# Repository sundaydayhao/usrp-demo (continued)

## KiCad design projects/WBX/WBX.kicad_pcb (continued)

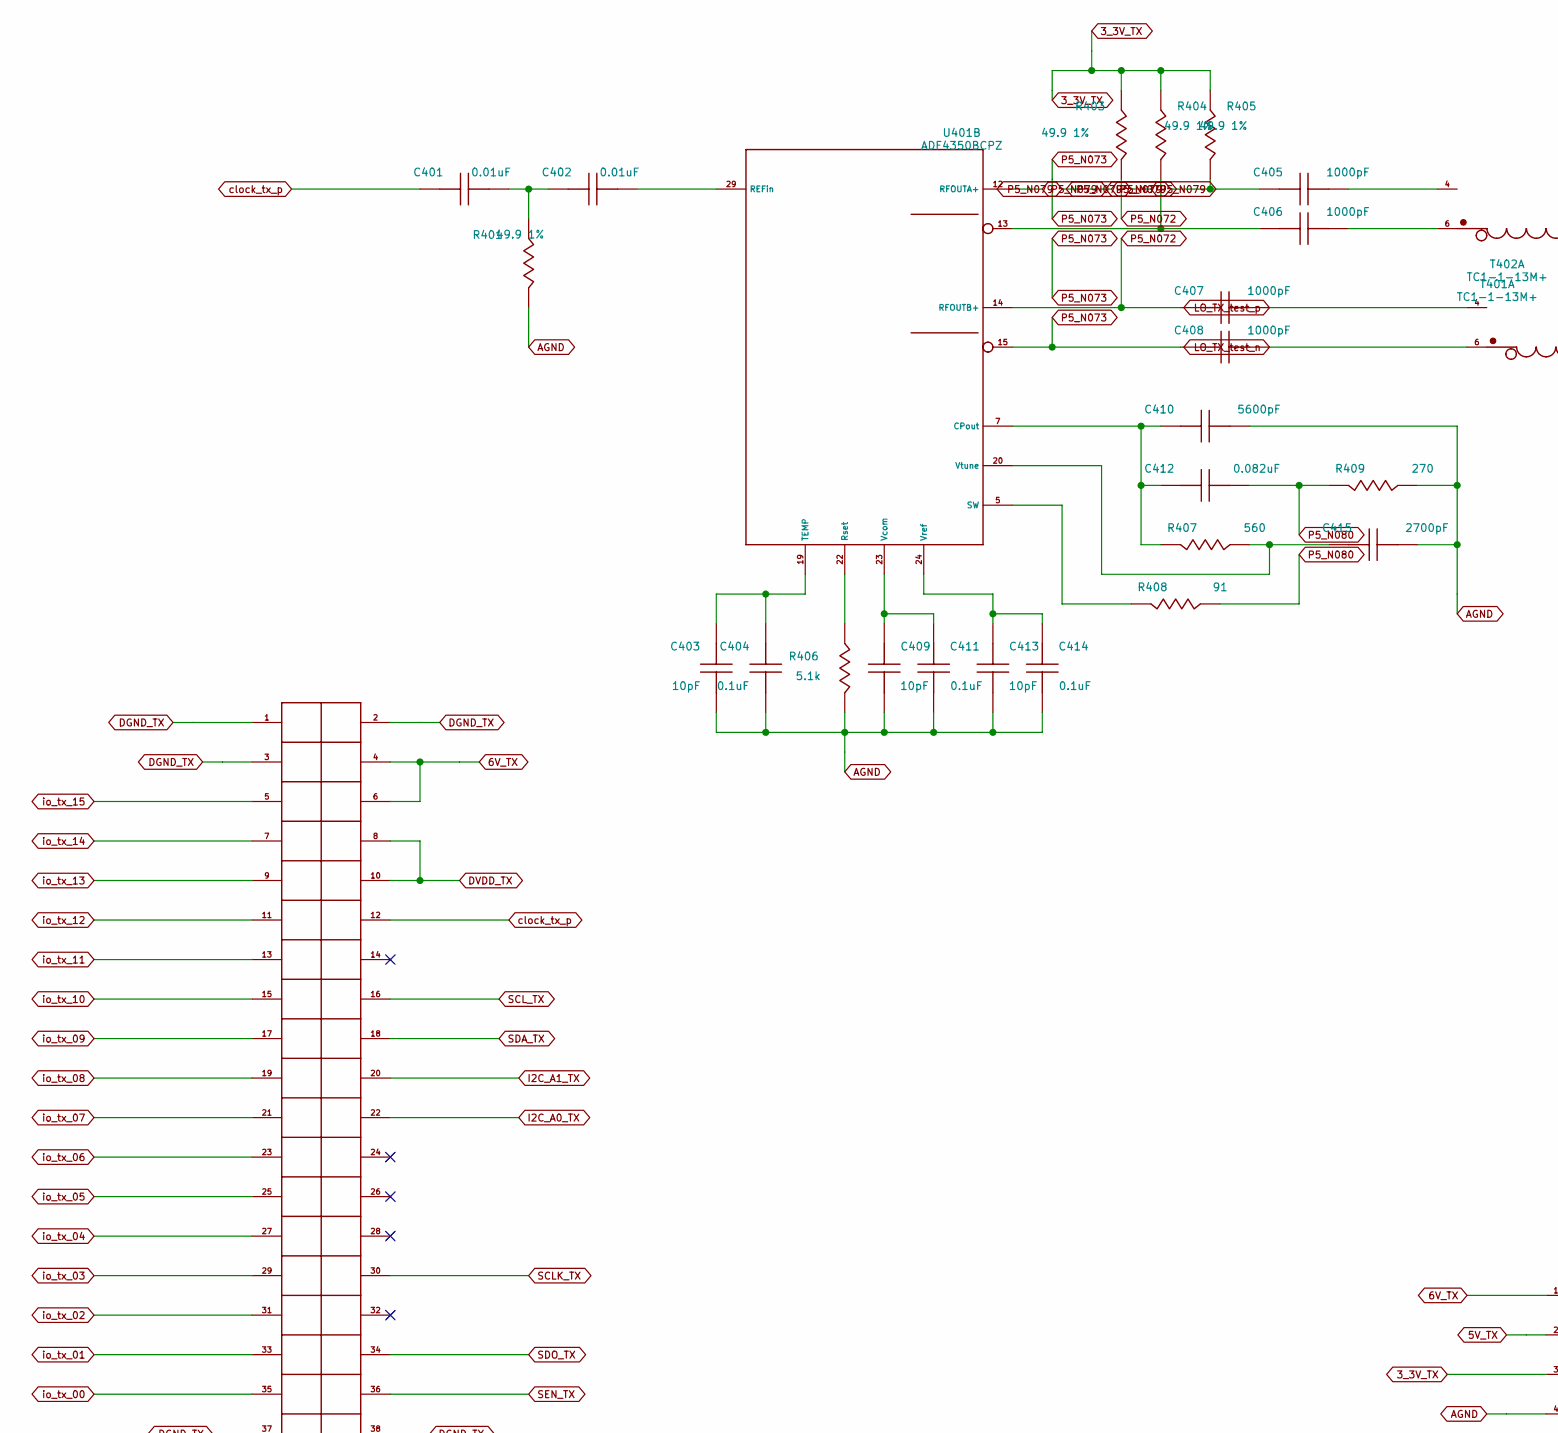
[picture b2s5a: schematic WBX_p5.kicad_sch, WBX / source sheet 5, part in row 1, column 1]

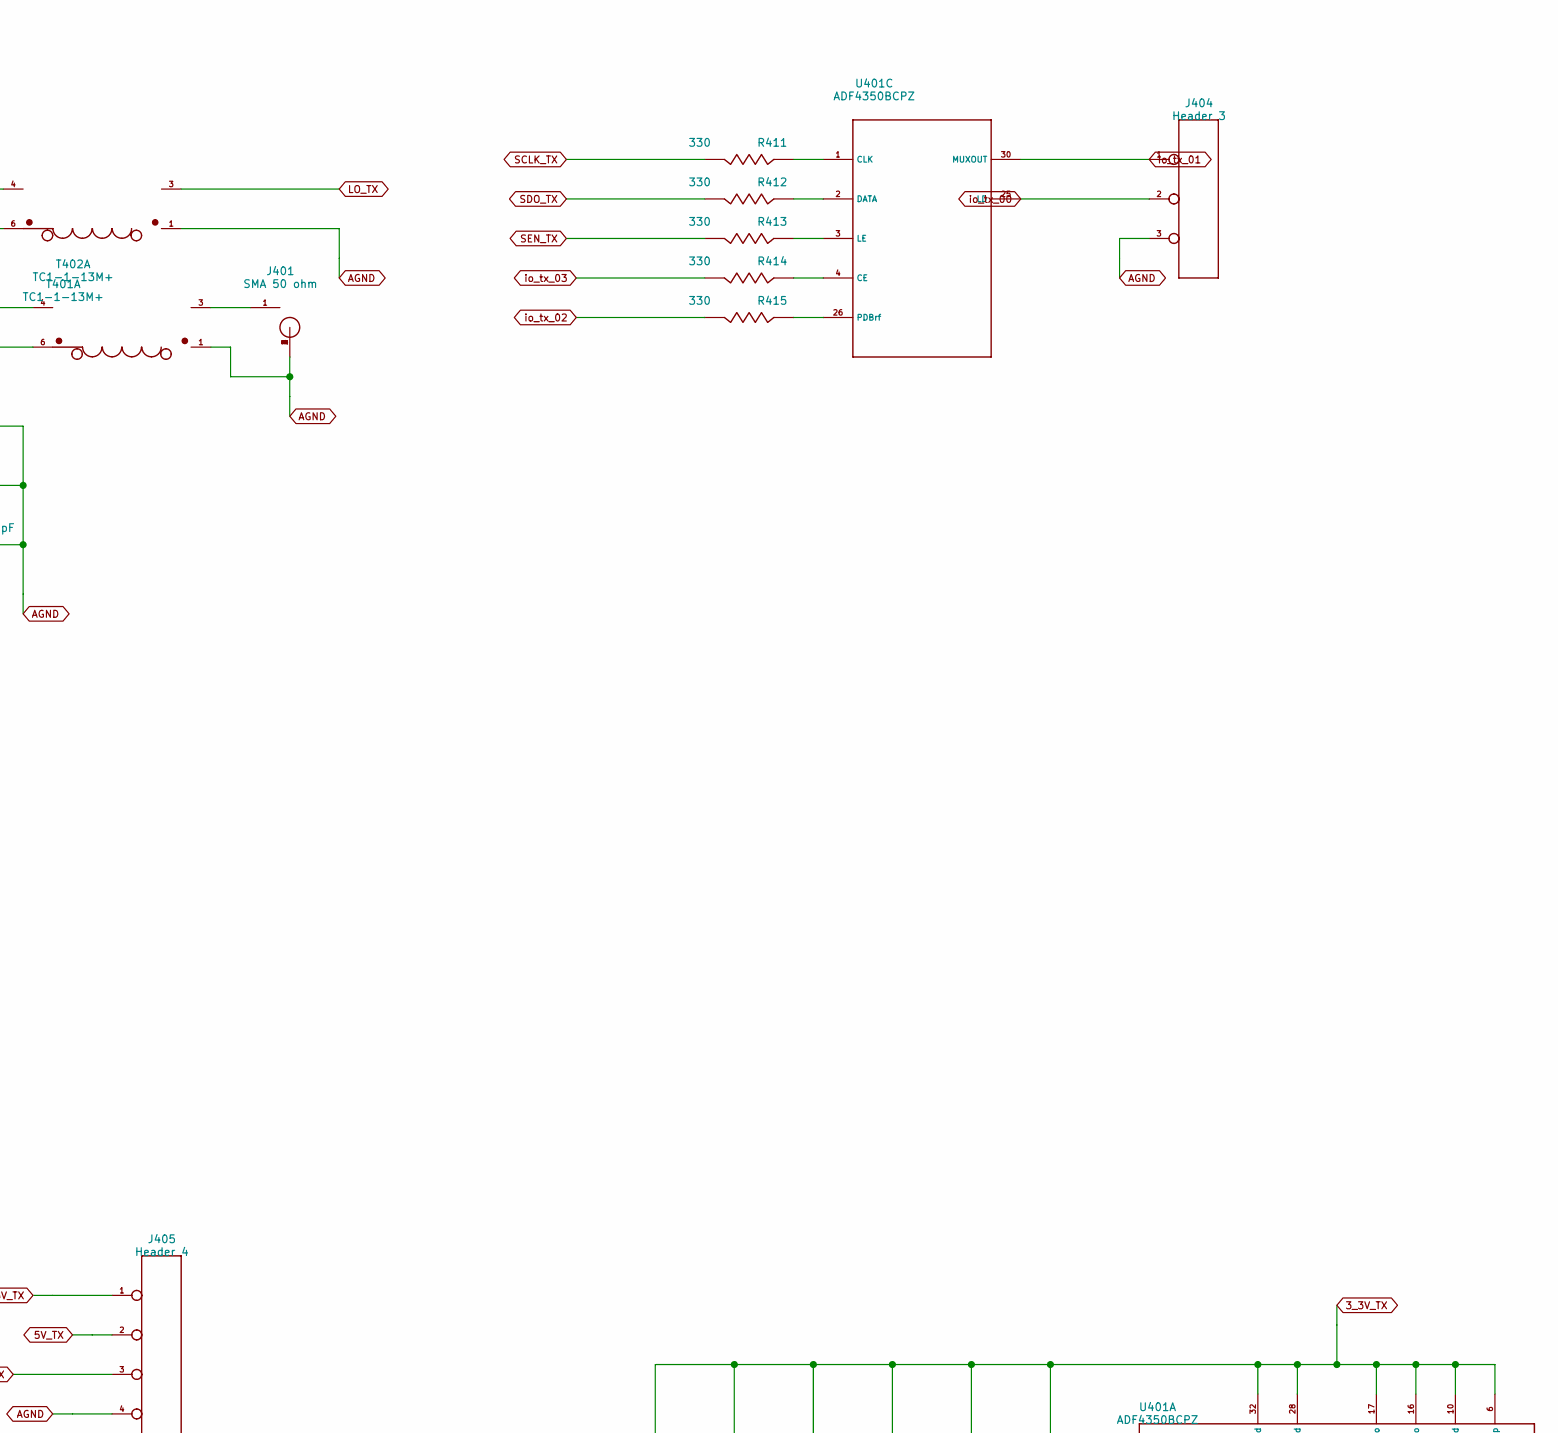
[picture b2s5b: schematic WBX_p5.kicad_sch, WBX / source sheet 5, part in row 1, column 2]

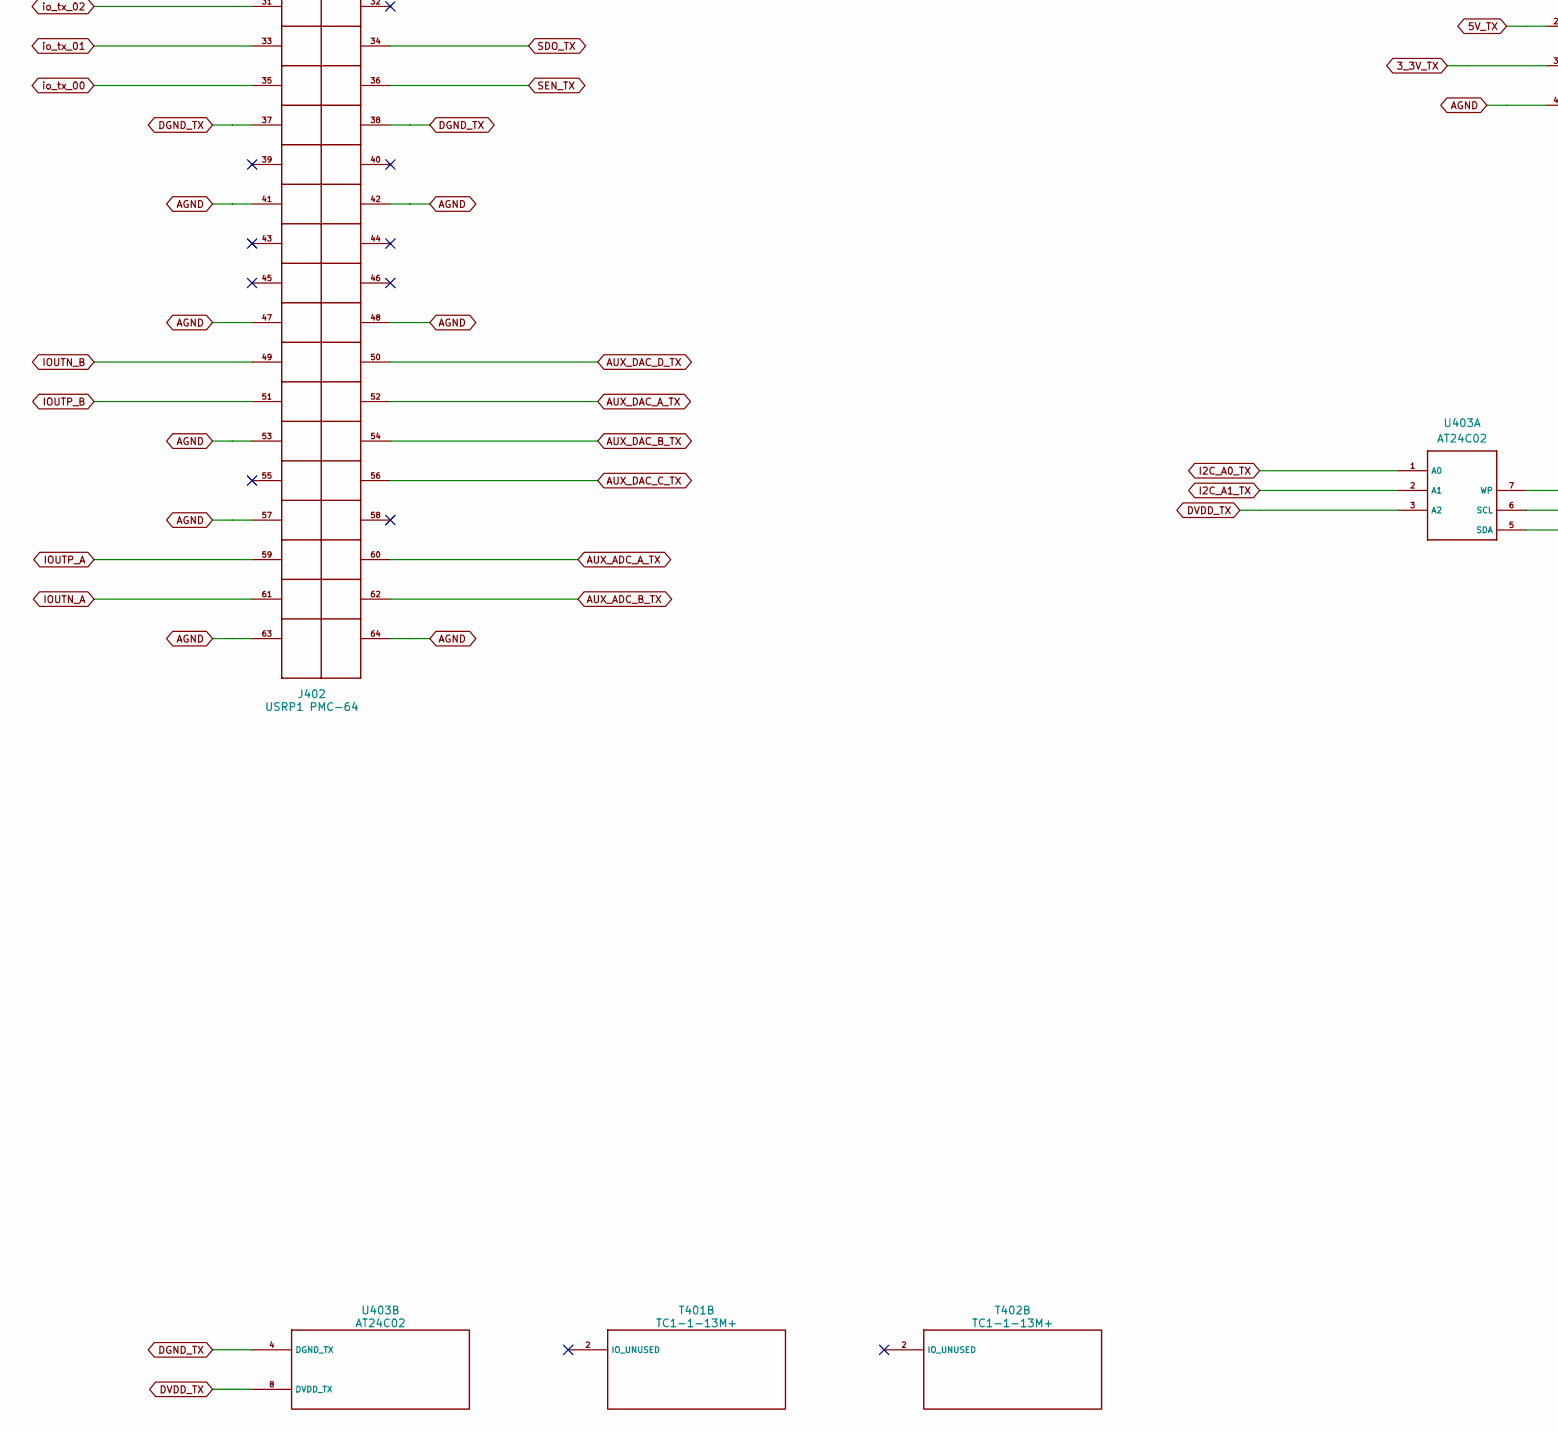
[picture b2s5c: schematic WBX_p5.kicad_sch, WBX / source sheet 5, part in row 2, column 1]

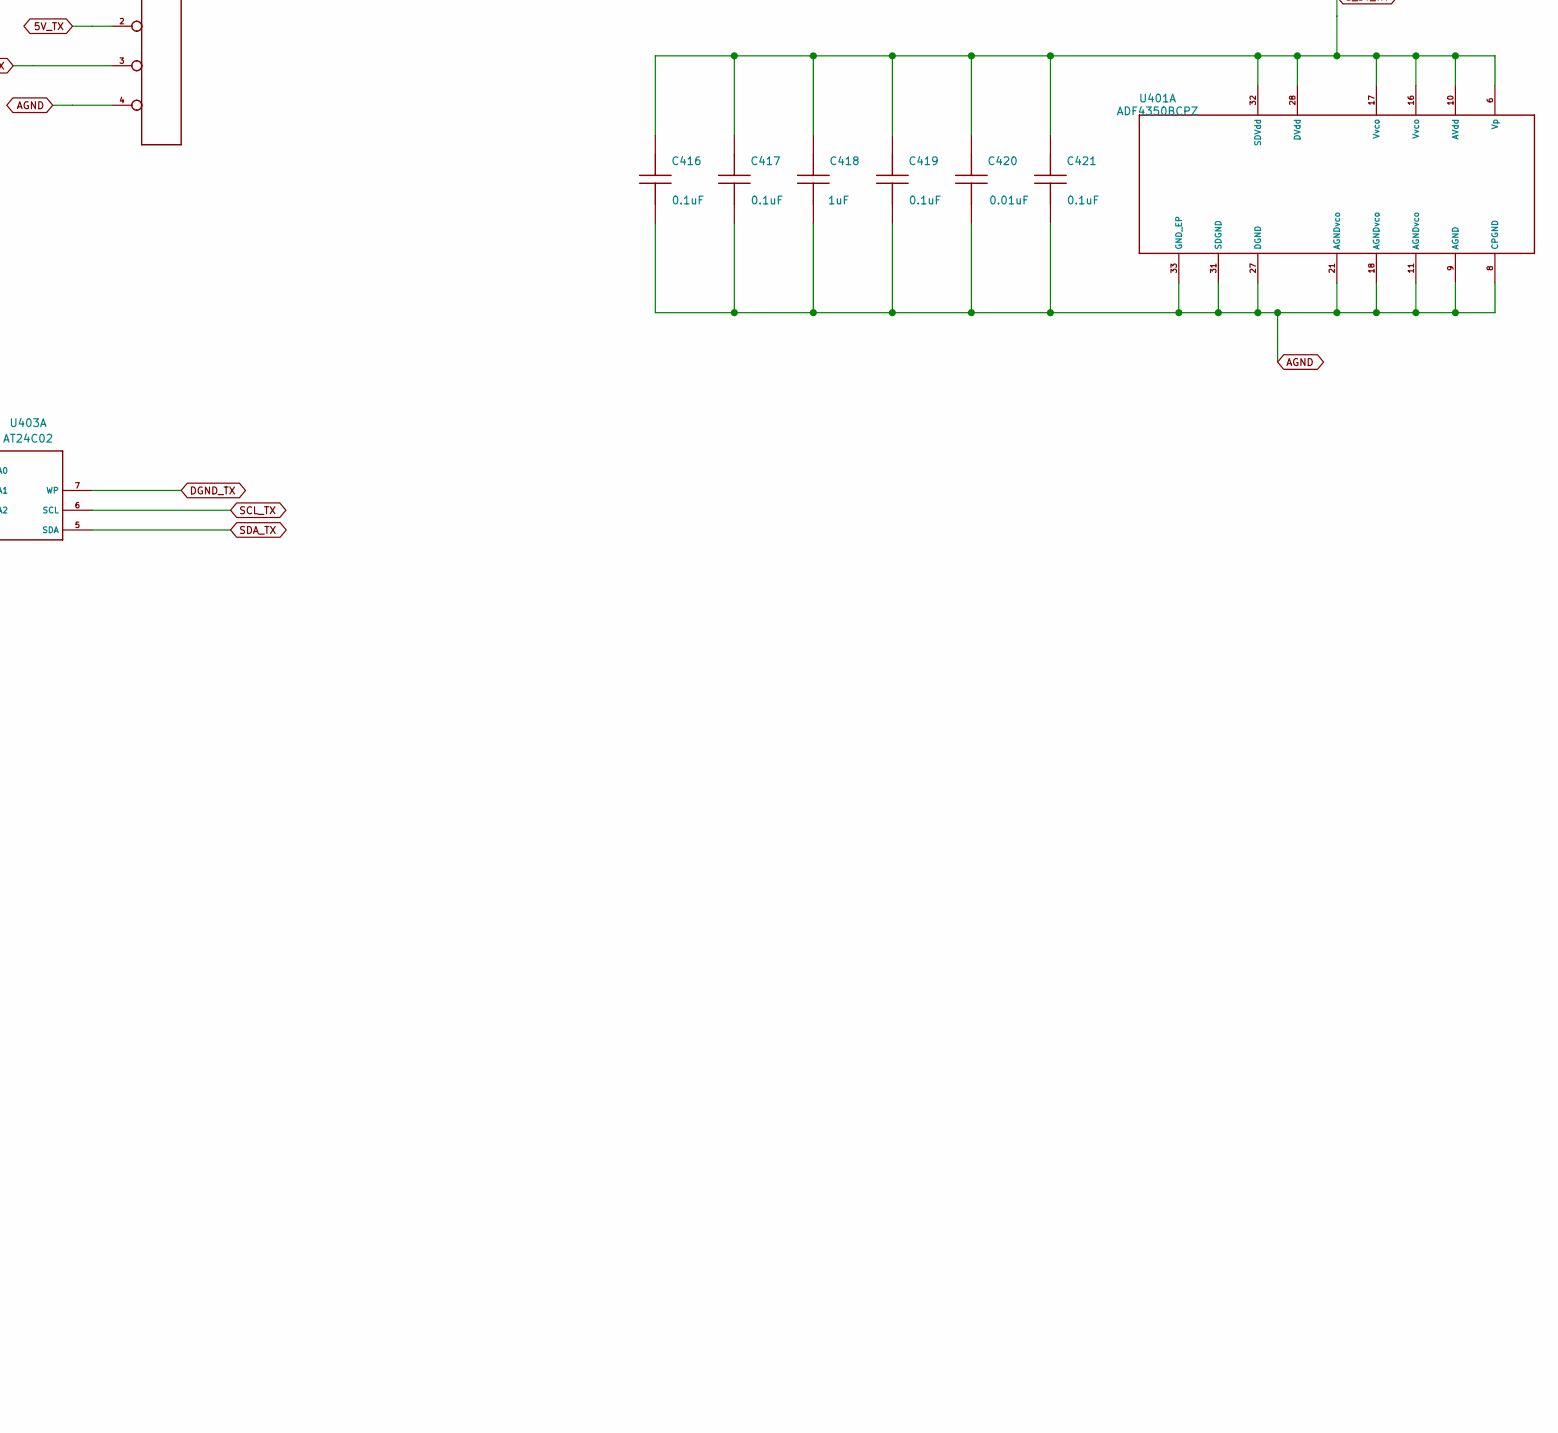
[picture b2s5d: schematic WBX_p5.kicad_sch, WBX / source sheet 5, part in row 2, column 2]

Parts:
C401: 0.01uF; C401
C402: 0.01uF; C402
C403: 10pF; C403
C404: 0.1uF; C404
C405: 1000pF; C405
C406: 1000pF; C406
C407: 1000pF; C407
C408: 1000pF; C408
C409: 10pF; C409
C410: 5600pF; C410
C411: 0.1uF; C411
C412: 0.082uF; C412
C413: 10pF; C413
C414: 0.1uF; C414
C415: 2700pF; C415
C416: 0.1uF; C416; MPN CL05B104KO5NNNC; LCSC C1525
C417: 0.1uF; C417; MPN CL05B104KO5NNNC; LCSC C1525
C418: 1uF; C418
C419: 0.1uF; C419; MPN CL05B104KO5NNNC; LCSC C1525
C420: 0.01uF; C420
C421: 0.1uF; C421; MPN CL05B104KO5NNNC; LCSC C1525
J401: SMA 50 ohm; J401
J402: USRP1 PMC-64; J402
J404: Header 3; J404
J405: Header 4; J405
R401: 49.9 1%; R401
R403: 49.9 1%; R403
R404: 49.9 1%; R404
R405: 49.9 1%; R405
R406: 5.1k; R406
R407: 560; R407
R408: 91; R408
R409: 270; R409
R411: 330; R411
R412: 330; R412
R413: 330; R413
R414: 330; R414
R415: 330; R415
T401: TC1-1-13M+; T401; MPN TC1-1-13M+
T402: TC1-1-13M+; T402; MPN TC1-1-13M+
U401: ADF4350BCPZ; U401; MPN ADF4350BCPZ
U403: AT24C02; U403; MPN AT24C02C-SSHM-T; LCSC C6203

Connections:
3_3V_TX: C416.1, C417.1, C418.1, C419.1, C420.1, C421.1, J405.3, R403.1, R404.1, R405.1, U401.6 (Vp), U401.10 (AVdd), U401.16 (Vvco), U401.17 (Vvco), U401.28 (DVdd), U401.32 (SDVdd); also elsewhere on the board
5V_TX: J405.2; also elsewhere on the board
6V_TX: J402.4, J402.6, J405.1; also elsewhere on the board
AGND: C403.2, C404.2, C409.2, C410.1, C411.2, C413.2, C414.2, C415.1, C416.2, C417.2, C418.2, C419.2, C420.2, C421.2, J401.2, J401.3, J401.4, J401.5, J402.41, J402.42, J402.47, J402.48, J402.53, J402.57, J402.63, J402.64, J404.3, J405.4, R401.2, R406.2, R409.1, T401.1, T402.1, U401.8 (CPGND), U401.9 (AGND), U401.11 (AGNDvco), U401.18 (AGNDvco), U401.21 (AGNDvco), U401.27 (DGND), U401.31 (SDGND), U401.33 (GND_EP); also elsewhere on the board
AUX_ADC_A_TX: J402.60; also elsewhere on the board
AUX_ADC_B_TX: J402.62; also elsewhere on the board
AUX_DAC_A_TX: J402.52; also elsewhere on the board
AUX_DAC_B_TX: J402.54; also elsewhere on the board
AUX_DAC_C_TX: J402.56
AUX_DAC_D_TX: J402.50
DGND_TX: J402.1, J402.2, J402.3, J402.37, J402.38, U403.4 (DGND_TX), U403.7 (WP)
DVDD_TX: J402.8, J402.10, U403.3 (A2), U403.8 (DVDD_TX)
I2C_A0_TX: J402.22, U403.1 (A0)
I2C_A1_TX: J402.20, U403.2 (A1); also elsewhere on the board
IOUTN_A: J402.61; also elsewhere on the board
IOUTN_B: J402.49; also elsewhere on the board
IOUTP_A: J402.59; also elsewhere on the board
IOUTP_B: J402.51; also elsewhere on the board
LO_TX: T402.3; also elsewhere on the board
LO_TX_test_n: C408.1, T401.6
LO_TX_test_p: C407.1, T401.4
unnamed: C401.1, C402.2, R401.1
unnamed: C405.1, T402.4
unnamed: C406.1, T402.6
unnamed: C406.2, R404.2, U401.13
unnamed: J401.1, T401.3
unnamed: C410.2, C412.2, R407.2, U401.7 (CPout)
unnamed: C402.1, U401.29 (REFin)
unnamed: R406.1, U401.22 (Rset)
unnamed: R408.2, U401.5 (SW)
unnamed: C403.1, C404.1, U401.19 (TEMP)
unnamed: C409.1, C411.1, U401.23 (Vcom)
unnamed: C413.1, C414.1, U401.24 (Vref)
unnamed: C415.2, R407.1, U401.20 (Vtune)
unnamed: R414.1, U401.4 (CE)
unnamed: R411.1, U401.1 (CLK)
unnamed: R412.1, U401.2 (DATA)
unnamed: R413.1, U401.3 (LE)
unnamed: R415.1, U401.26 (PDBrf)
P5_N072: C407.2, R403.2, U401.14 (RFOUTB+)
P5_N073: C408.2, U401.15
P5_N079: C405.2, R405.2, U401.12 (RFOUTA+)
P5_N080: C412.1, R408.1, R409.2
SCLK_TX: J402.30, R411.2
SCL_TX: J402.16, U403.6 (SCL); also elsewhere on the board
SDA_TX: J402.18, U403.5 (SDA); also elsewhere on the board
SDO_TX: J402.34, R412.2
SEN_TX: J402.36, R413.2
clock_tx_p: C401.2, J402.12
io_tx_00: J402.35, J404.2, U401.25 (LD)
io_tx_01: J402.33, J404.1, U401.30 (MUXOUT)
io_tx_02: J402.31, R415.2
io_tx_03: J402.29, R414.2
io_tx_04: J402.27; also elsewhere on the board
io_tx_05: J402.25; also elsewhere on the board
io_tx_06: J402.23; also elsewhere on the board
io_tx_07: J402.21; also elsewhere on the board
io_tx_08: J402.19; also elsewhere on the board
io_tx_09: J402.17; also elsewhere on the board
io_tx_10: J402.15; also elsewhere on the board
io_tx_11: J402.13; also elsewhere on the board
io_tx_12: J402.11; also elsewhere on the board
io_tx_13: J402.9; also elsewhere on the board
io_tx_14: J402.7; also elsewhere on the board
io_tx_15: J402.5; also elsewhere on the board

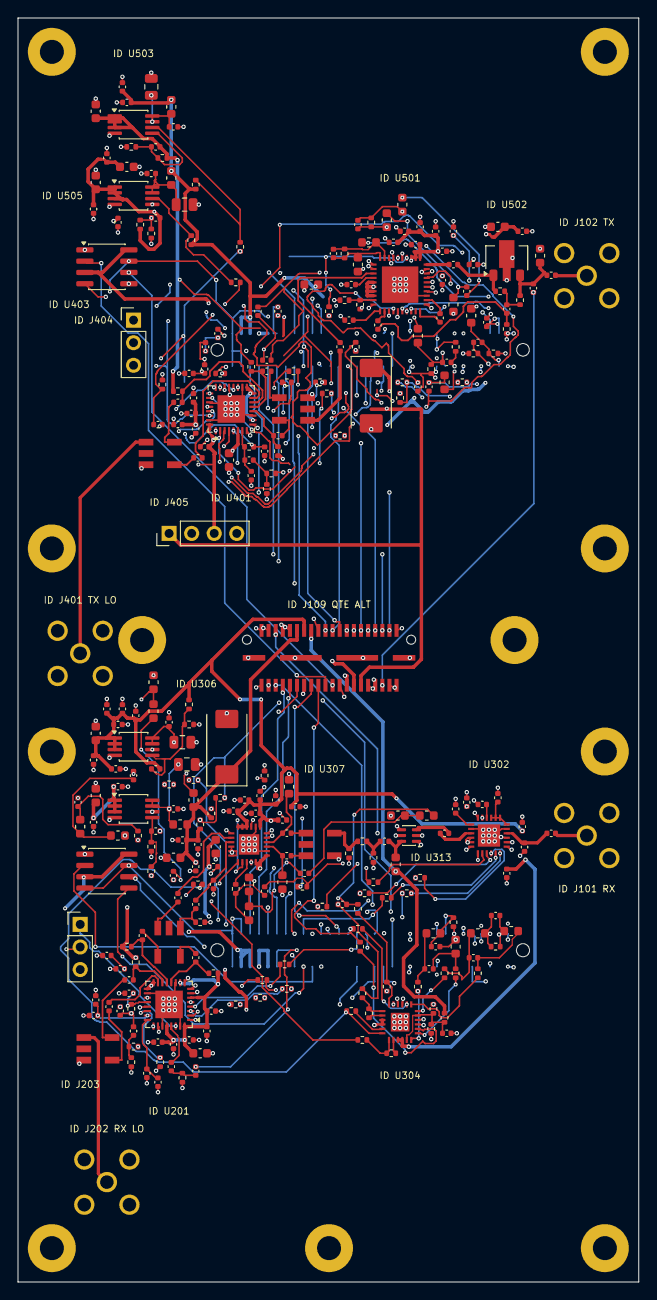
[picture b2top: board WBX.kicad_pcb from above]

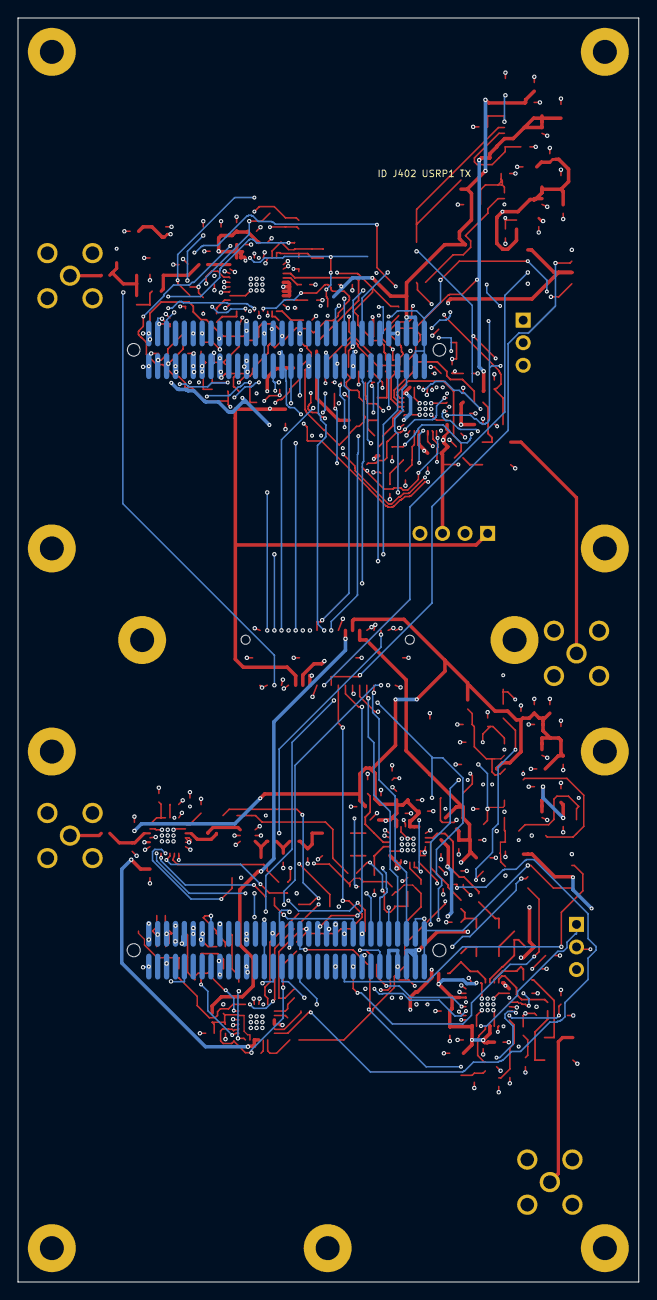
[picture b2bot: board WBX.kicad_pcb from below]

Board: 6 copper layers, 69.8 x 142.2 mm, 302 parts (2 on the bottom side), 226 nets.

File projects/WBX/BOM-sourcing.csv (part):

Reference,Value,Footprint,Manufacturer,MPN,LCSC,Sourcing_status,Specification,Source_value,Evidence,Approved_brands,Sourcing_policy
C101,NONE,USRP:C101,,,,DNP 不装,保留调试/选配焊盘,NONE,,,
C102,NONE,USRP:C102,,,,DNP 不装,保留调试/选配焊盘,NONE,,,
C103,1000pF,USRP:C103,候选：Murata / TDK / Samsung Electro-Mechanics / Walsin / FH / EYANG,,,0402 按参数选型，待锁定料号,0402; 匹配和调谐电容用 C0G，保留原容差；去耦用 X7R >=16 V,1000pF,,Murata / TDK / Samsung Electro-Mechanics / Walsin / FH / EYANG,国产与国际品牌均可；满足参数后比较含税到手价、起订量、库存和交期；换料须复核封装及电气指标
C104,1000pF,USRP:C104,候选：Murata / TDK / Samsung Electro-Mechanics / Walsin / FH / EYANG,,,0402 按参数选型，待锁定料号,0402; 匹配和调谐电容用 C0G，保留原容差；去耦用 X7R >=16 V,1000pF,,Murata / TDK / Samsung Electro-Mechanics / Walsin / FH / EYANG,国产与国际品牌均可；满足参数后比较含税到手价、起订量、库存和交期；换料须复核封装及电气指标
C201,0.01uF,USRP:C201,候选：Murata / TDK / Samsung Electro-Mechanics / Walsin / FH / EYANG,,,0402 按参数选型，待锁定料号,0402; 匹配和调谐电容用 C0G，保留原容差；去耦用 X7R >=16 V,0.01uF,,Murata / TDK / Samsung Electro-Mechanics / Walsin / FH / EYANG,国产与国际品牌均可；满足参数后比较含税到手价、起订量、库存和交期；换料须复核封装及电气指标
C202,0.01uF,USRP:C202,候选：Murata / TDK / Samsung Electro-Mechanics / Walsin / FH / EYANG,,,0402 按参数选型，待锁定料号,0402; 匹配和调谐电容用 C0G，保留原容差；去耦用 X7R >=16 V,0.01uF,,Murata / TDK / Samsung Electro-Mechanics / Walsin / FH / EYANG,国产与国际品牌均可；满足参数后比较含税到手价、起订量、库存和交期；换料须复核封装及电气指标
C203,10pF,USRP:C203,候选：Murata / TDK / Samsung Electro-Mechanics / Walsin / FH / EYANG,,,0402 按参数选型，待锁定料号,0402; 匹配和调谐电容用 C0G，保留原容差；去耦用 X7R >=16 V,10pF,,Murata / TDK / Samsung Electro-Mechanics / Walsin / FH / EYANG,国产与国际品牌均可；满足参数后比较含税到手价、起订量、库存和交期；换料须复核封装及电气指标
C204,0.1uF,USRP:C204,候选：Murata / TDK / Samsung Electro-Mechanics / Walsin / FH / EYANG,,,0402 按参数选型，待锁定料号,0402; 匹配和调谐电容用 C0G，保留原容差；去耦用 X7R >=16 V,0.1uF,,Murata / TDK / Samsung Electro-Mechanics / Walsin / FH / EYANG,国产与国际品牌均可；满足参数后比较含税到手价、起订量、库存和交期；换料须复核封装及电气指标
C205,1000pF,USRP:C205,候选：Murata / TDK / Samsung Electro-Mechanics / Walsin / FH / EYANG,,,0402 按参数选型，待锁定料号,0402; 匹配和调谐电容用 C0G，保留原容差；去耦用 X7R >=16 V,1000pF,,Murata / TDK / Samsung Electro-Mechanics / Walsin / FH / EYANG,国产与国际品牌均可；满足参数后比较含税到手价、起订量、库存和交期；换料须复核封装及电气指标
C206,1000pF,USRP:C206,候选：Murata / TDK / Samsung Electro-Mechanics / Walsin / FH / EYANG,,,0402 按参数选型，待锁定料号,0402; 匹配和调谐电容用 C0G，保留原容差；去耦用 X7R >=16 V,1000pF,,Murata / TDK / Samsung Electro-Mechanics / Walsin / FH / EYANG,国产与国际品牌均可；满足参数后比较含税到手价、起订量、库存和交期；换料须复核封装及电气指标
C207,1000pF,USRP:C207,候选：Murata / TDK / Samsung Electro-Mechanics / Walsin / FH / EYANG,,,0402 按参数选型，待锁定料号,0402; 匹配和调谐电容用 C0G，保留原容差；去耦用 X7R >=16 V,1000pF,,Murata / TDK / Samsung Electro-Mechanics / Walsin / FH / EYANG,国产与国际品牌均可；满足参数后比较含税到手价、起订量、库存和交期；换料须复核封装及电气指标
C208,1000pF,USRP:C208,候选：Murata / TDK / Samsung Electro-Mechanics / Walsin / FH / EYANG,,,0402 按参数选型，待锁定料号,0402; 匹配和调谐电容用 C0G，保留原容差；去耦用 X7R >=16 V,1000pF,,Murata / TDK / Samsung Electro-Mechanics / Walsin / FH / EYANG,国产与国际品牌均可；满足参数后比较含税到手价、起订量、库存和交期；换料须复核封装及电气指标
C209,10pF,USRP:C209,候选：Murata / TDK / Samsung Electro-Mechanics / Walsin / FH / EYANG,,,0402 按参数选型，待锁定料号,0402; 匹配和调谐电容用 C0G，保留原容差；去耦用 X7R >=16 V,10pF,,Murata / TDK / Samsung Electro-Mechanics / Walsin / FH / EYANG,国产与国际品牌均可；满足参数后比较含税到手价、起订量、库存和交期；换料须复核封装及电气指标
C210,5600pF,USRP:C210,候选：Murata / TDK / Samsung Electro-Mechanics / Walsin / FH / EYANG,,,0402 按参数选型，待锁定料号,0402; 匹配和调谐电容用 C0G，保留原容差；去耦用 X7R >=16 V,5600pF,,Murata / TDK / Samsung Electro-Mechanics / Walsin / FH / EYANG,国产与国际品牌均可；满足参数后比较含税到手价、起订量、库存和交期；换料须复核封装及电气指标
C211,0.1uF,USRP:C211,候选：Murata / TDK / Samsung Electro-Mechanics / Walsin / FH / EYANG,,,0402 按参数选型，待锁定料号,0402; 匹配和调谐电容用 C0G，保留原容差；去耦用 X7R >=16 V,0.1uF,,Murata / TDK / Samsung Electro-Mechanics / Walsin / FH / EYANG,国产与国际品牌均可；满足参数后比较含税到手价、起订量、库存和交期；换料须复核封装及电气指标
C212,0.082uF,USRP:C212,候选：Murata / TDK / Samsung Electro-Mechanics / Walsin / FH / EYANG,,,0402 按参数选型，待锁定料号,0402; 匹配和调谐电容用 C0G，保留原容差；去耦用 X7R >=16 V,0.082uF,,Murata / TDK / Samsung Electro-Mechanics / Walsin / FH / EYANG,国产与国际品牌均可；满足参数后比较含税到手价、起订量、库存和交期；换料须复核封装及电气指标
C213,10pF,USRP:C213,候选：Murata / TDK / Samsung Electro-Mechanics / Walsin / FH / EYANG,,,0402 按参数选型，待锁定料号,0402; 匹配和调谐电容用 C0G，保留原容差；去耦用 X7R >=16 V,10pF,,Murata / TDK / Samsung Electro-Mechanics / Walsin / FH / EYANG,国产与国际品牌均可；满足参数后比较含税到手价、起订量、库存和交期；换料须复核封装及电气指标
C214,0.1uF,USRP:C214,候选：Murata / TDK / Samsung Electro-Mechanics / Walsin / FH / EYANG,,,0402 按参数选型，待锁定料号,0402; 匹配和调谐电容用 C0G，保留原容差；去耦用 X7R >=16 V,0.1uF,,Murata / TDK / Samsung Electro-Mechanics / Walsin / FH / EYANG,国产与国际品牌均可；满足参数后比较含税到手价、起订量、库存和交期；换料须复核封装及电气指标
C215,2700pF,USRP:C215,候选：Murata / TDK / Samsung Electro-Mechanics / Walsin / FH / EYANG,,,0402 按参数选型，待锁定料号,0402; 匹配和调谐电容用 C0G，保留原容差；去耦用 X7R >=16 V,2700pF,,Murata / TDK / Samsung Electro-Mechanics / Walsin / FH / EYANG,国产与国际品牌均可；满足参数后比较含税到手价、起订量、库存和交期；换料须复核封装及电气指标
C216,0.1uF,USRP:C216,Samsung Electro-Mechanics,CL05B104KO5NNNC,C1525,已核对0402与电源对地去耦连接；待实机电源噪声验证,0402; 100 nF; X7R; 16 V; +/-10%; 电源去耦；需考虑直流偏压降容,0.1uF,https://datasheet.lcsc.com/datasheet/pdf/02336ea48ea44ca18c7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,Murata / TDK / Samsung Electro-Mechanics / Walsin / FH / EYANG,国产与国际品牌均可；满足参数后比较含税到手价、起订量、库存和交期；换料须复核封装及电气指标
C217,0.1uF,USRP:C217,Samsung Electro-Mechanics,CL05B104KO5NNNC,C1525,已核对0402与电源对地去耦连接；待实机电源噪声验证,0402; 100 nF; X7R; 16 V; +/-10%; 电源去耦；需考虑直流偏压降容,0.1uF,https://datasheet.lcsc.com/datasheet/pdf/02336ea48ea44ca18c7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,Murata / TDK / Samsung Electro-Mechanics / Walsin / FH / EYANG,国产与国际品牌均可；满足参数后比较含税到手价、起订量、库存和交期；换料须复核封装及电气指标
C218,1uF,USRP:C218,候选：Murata / TDK / Samsung Electro-Mechanics / Walsin / FH / EYANG,,,规格选型，待锁定料号,按项目焊盘尺寸；RF/匹配/PLL环路优先 C0G；去耦 X7R；耐压 >=16 V；保留原容差,1uF,,Murata / TDK / Samsung Electro-Mechanics / Walsin / FH / EYANG,国产与国际品牌均可；满足参数后比较含税到手价、起订量、库存和交期；换料须复核封装及电气指标
C219,0.1uF,USRP:C219,Samsung Electro-Mechanics,CL05B104KO5NNNC,C1525,已核对0402与电源对地去耦连接；待实机电源噪声验证,0402; 100 nF; X7R; 16 V; +/-10%; 电源去耦；需考虑直流偏压降容,0.1uF,https://datasheet.lcsc.com/datasheet/pdf/02336ea48ea44ca18c7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,Murata / TDK / Samsung Electro-Mechanics / Walsin / FH / EYANG,国产与国际品牌均可；满足参数后比较含税到手价、起订量、库存和交期；换料须复核封装及电气指标
C220,0.01uF,USRP:C220,候选：Murata / TDK / Samsung Electro-Mechanics / Walsin / FH / EYANG,,,0402 按参数选型，待锁定料号,0402; 匹配和调谐电容用 C0G，保留原容差；去耦用 X7R >=16 V,0.01uF,,Murata / TDK / Samsung Electro-Mechanics / Walsin / FH / EYANG,国产与国际品牌均可；满足参数后比较含税到手价、起订量、库存和交期；换料须复核封装及电气指标
C221,0.1uF,USRP:C221,Samsung Electro-Mechanics,CL05B104KO5NNNC,C1525,已核对0402与电源对地去耦连接；待实机电源噪声验证,0402; 100 nF; X7R; 16 V; +/-10%; 电源去耦；需考虑直流偏压降容,0.1uF,https://datasheet.lcsc.com/datasheet/pdf/02336ea48ea44ca18c7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,Murata / TDK / Samsung Electro-Mechanics / Walsin / FH / EYANG,国产与国际品牌均可；满足参数后比较含税到手价、起订量、库存和交期；换料须复核封装及电气指标
C304,1000pF,USRP:C304,候选：Murata / TDK / Samsung Electro-Mechanics / Walsin / FH / EYANG,,,0402 按参数选型，待锁定料号,0402; 匹配和调谐电容用 C0G，保留原容差；去耦用 X7R >=16 V,1000pF,,Murata / TDK / Samsung Electro-Mechanics / Walsin / FH / EYANG,国产与国际品牌均可；满足参数后比较含税到手价、起订量、库存和交期；换料须复核封装及电气指标
C305,82pF 2%,USRP:C305,候选：Murata / TDK / Samsung Electro-Mechanics / Walsin / FH / EYANG,,,0402 按参数选型，待锁定料号,0402; 匹配和调谐电容用 C0G，保留原容差；去耦用 X7R >=16 V,82pF 2%,,Murata / TDK / Samsung Electro-Mechanics / Walsin / FH / EYANG,国产与国际品牌均可；满足参数后比较含税到手价、起订量、库存和交期；换料须复核封装及电气指标
C306,150pF 2%,USRP:C306,候选：Murata / TDK / Samsung Electro-Mechanics / Walsin / FH / EYANG,,,0402 按参数选型，待锁定料号,0402; 匹配和调谐电容用 C0G，保留原容差；去耦用 X7R >=16 V,150pF 2%,,Murata / TDK / Samsung Electro-Mechanics / Walsin / FH / EYANG,国产与国际品牌均可；满足参数后比较含税到手价、起订量、库存和交期；换料须复核封装及电气指标
C307,0.1uF,USRP:C307,Samsung Electro-Mechanics,CL05B104KO5NNNC,C1525,已核对0402与电源对地去耦连接；待实机电源噪声验证,0402; 100 nF; X7R; 16 V; +/-10%; 电源去耦；需考虑直流偏压降容,0.1uF,https://datasheet.lcsc.com/datasheet/pdf/02336ea48ea44ca18c7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,Murata / TDK / Samsung Electro-Mechanics / Walsin / FH / EYANG,国产与国际品牌均可；满足参数后比较含税到手价、起订量、库存和交期；换料须复核封装及电气指标
C308,0.1uF,USRP:C308,Samsung Electro-Mechanics,CL05B104KO5NNNC,C1525,已核对0402与电源对地去耦连接；待实机电源噪声验证,0402; 100 nF; X7R; 16 V; +/-10%; 电源去耦；需考虑直流偏压降容,0.1uF,https://datasheet.lcsc.com/datasheet/pdf/02336ea48ea44ca18c7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,Murata / TDK / Samsung Electro-Mechanics / Walsin / FH / EYANG,国产与国际品牌均可；满足参数后比较含税到手价、起订量、库存和交期；换料须复核封装及电气指标
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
